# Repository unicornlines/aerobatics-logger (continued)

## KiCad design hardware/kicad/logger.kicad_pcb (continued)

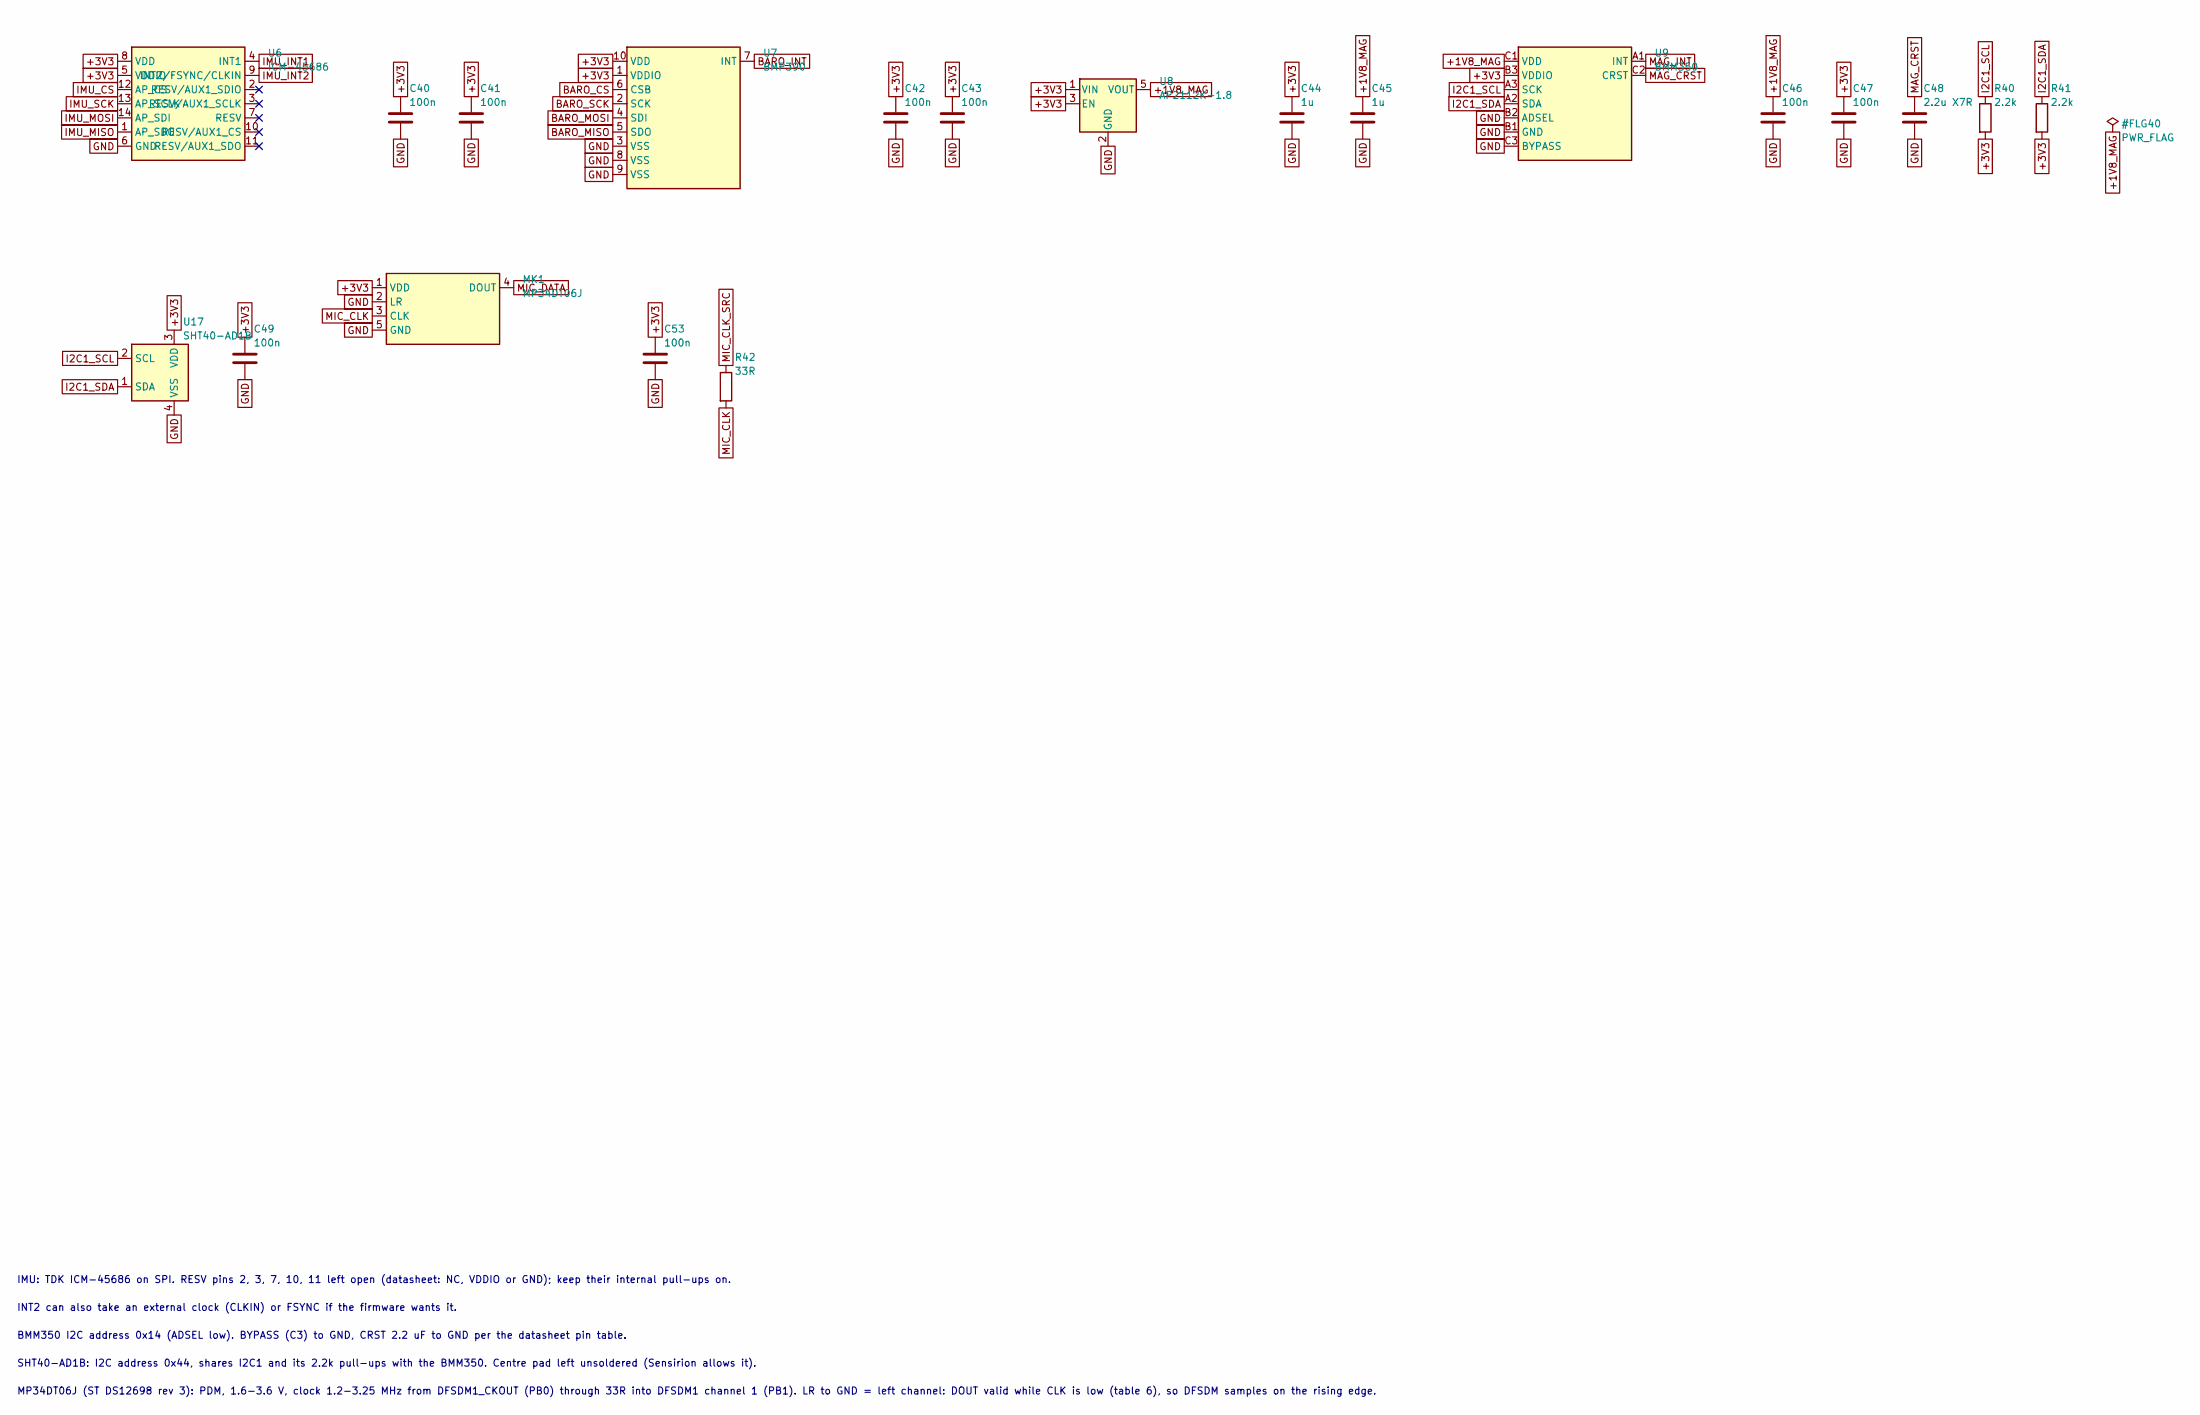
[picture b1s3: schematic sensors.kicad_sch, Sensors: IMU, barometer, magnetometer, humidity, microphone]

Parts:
C40, C41, C42, C43, C46, C47, C49, C53: 100n; C_0402_1005Metric
C44, C45: 1u; C_0402_1005Metric
C48: 2.2u X7R; C_0603_1608Metric
MK1: MP34DT06J; ST_HCLGA-4_3x4mm_MP34DT06J; MPN MP34DT06JTR
R40, R41: 2.2k; R_0402_1005Metric
R42: 33R; R_0402_1005Metric
U6: ICM-45686; LGA-14_3x2.5mm_P0.5mm_LayoutBorder3x4y
U7: BMP390; Bosch_LGA-10_2.0x2.0mm
U8: AP2112K-1.8; SOT-23-5
U9: BMM350; Bosch_WLCSP-9_1.28x1.28mm_P0.4mm
U17: SHT40-AD1B; Sensirion_DFN-4_1.5x1.5mm_P0.8mm_SHT4x_NoCentralPad; MPN SHT40-AD1B-R3

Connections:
+1V8_MAG: C45.1, C46.1, U8.5 (VOUT), U9.C1 (VDD)
+3V3: C40.1, C41.1, C42.1, C43.1, C44.1, C47.1, C49.1, C53.1, MK1.1 (VDD), R40.2, R41.2, U6.5 (VDDIO), U6.8 (VDD), U7.1 (VDDIO), U7.10 (VDD), U8.1 (VIN), U8.3 (EN), U9.B3 (VDDIO), U17.3 (VDD); also elsewhere on the board
BARO_CS: U7.6 (CSB); also elsewhere on the board
BARO_INT: U7.7 (INT); also elsewhere on the board
BARO_MISO: U7.5 (SDO); also elsewhere on the board
BARO_MOSI: U7.4 (SDI); also elsewhere on the board
BARO_SCK: U7.2 (SCK); also elsewhere on the board
GND: C40.2, C41.2, C42.2, C43.2, C44.2, C45.2, C46.2, C47.2, C48.2, C49.2, C53.2, MK1.2 (LR), MK1.5 (GND), MK1.6 (GND), MK1.7 (GND), MK1.8 (GND), U6.6 (GND), U7.3 (VSS), U7.8 (VSS), U7.9 (VSS), U8.2 (GND), U9.B1 (GND), U9.B2 (ADSEL), U9.C3 (BYPASS), U17.4 (VSS); also elsewhere on the board
I2C1_SCL: R40.1, U9.A3 (SCK), U17.2 (SCL); also elsewhere on the board
I2C1_SDA: R41.1, U9.A2 (SDA), U17.1 (SDA); also elsewhere on the board
IMU_CS: U6.12 (AP_CS); also elsewhere on the board
IMU_INT1: U6.4 (INT1); also elsewhere on the board
IMU_INT2: U6.9 (INT2/FSYNC/CLKIN); also elsewhere on the board
IMU_MISO: U6.1 (AP_SDO); also elsewhere on the board
IMU_MOSI: U6.14 (AP_SDI); also elsewhere on the board
IMU_SCK: U6.13 (AP_SCLK); also elsewhere on the board
MAG_CRST: C48.1, U9.C2 (CRST)
MAG_INT: U9.A1 (INT); also elsewhere on the board
MIC_CLK: MK1.3 (CLK), R42.2
MIC_CLK_SRC: R42.1; also elsewhere on the board
MIC_DATA: MK1.4 (DOUT); also elsewhere on the board

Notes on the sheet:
IMU: TDK ICM-45686 on SPI. RESV pins 2, 3, 7, 10, 11 left open (datasheet: NC, VDDIO or GND); keep their internal pull-ups on.
INT2 can also take an external clock (CLKIN) or FSYNC if the firmware wants it.
BMM350 I2C address 0x14 (ADSEL low). BYPASS (C3) to GND, CRST 2.2 uF to GND per the datasheet pin table.
SHT40-AD1B: I2C address 0x44, shares I2C1 and its 2.2k pull-ups with the BMM350. Centre pad left unsoldered (Sensirion allows it).
MP34DT06J (ST DS12698 rev 3): PDM, 1.6-3.6 V, clock 1.2-3.25 MHz from DFSDM1_CKOUT (PB0) through 33R into DFSDM1 channel 1 (PB1). LR to GND = left channel: DOUT valid while CLK is low (table 6), so DFSDM samples on the rising edge.

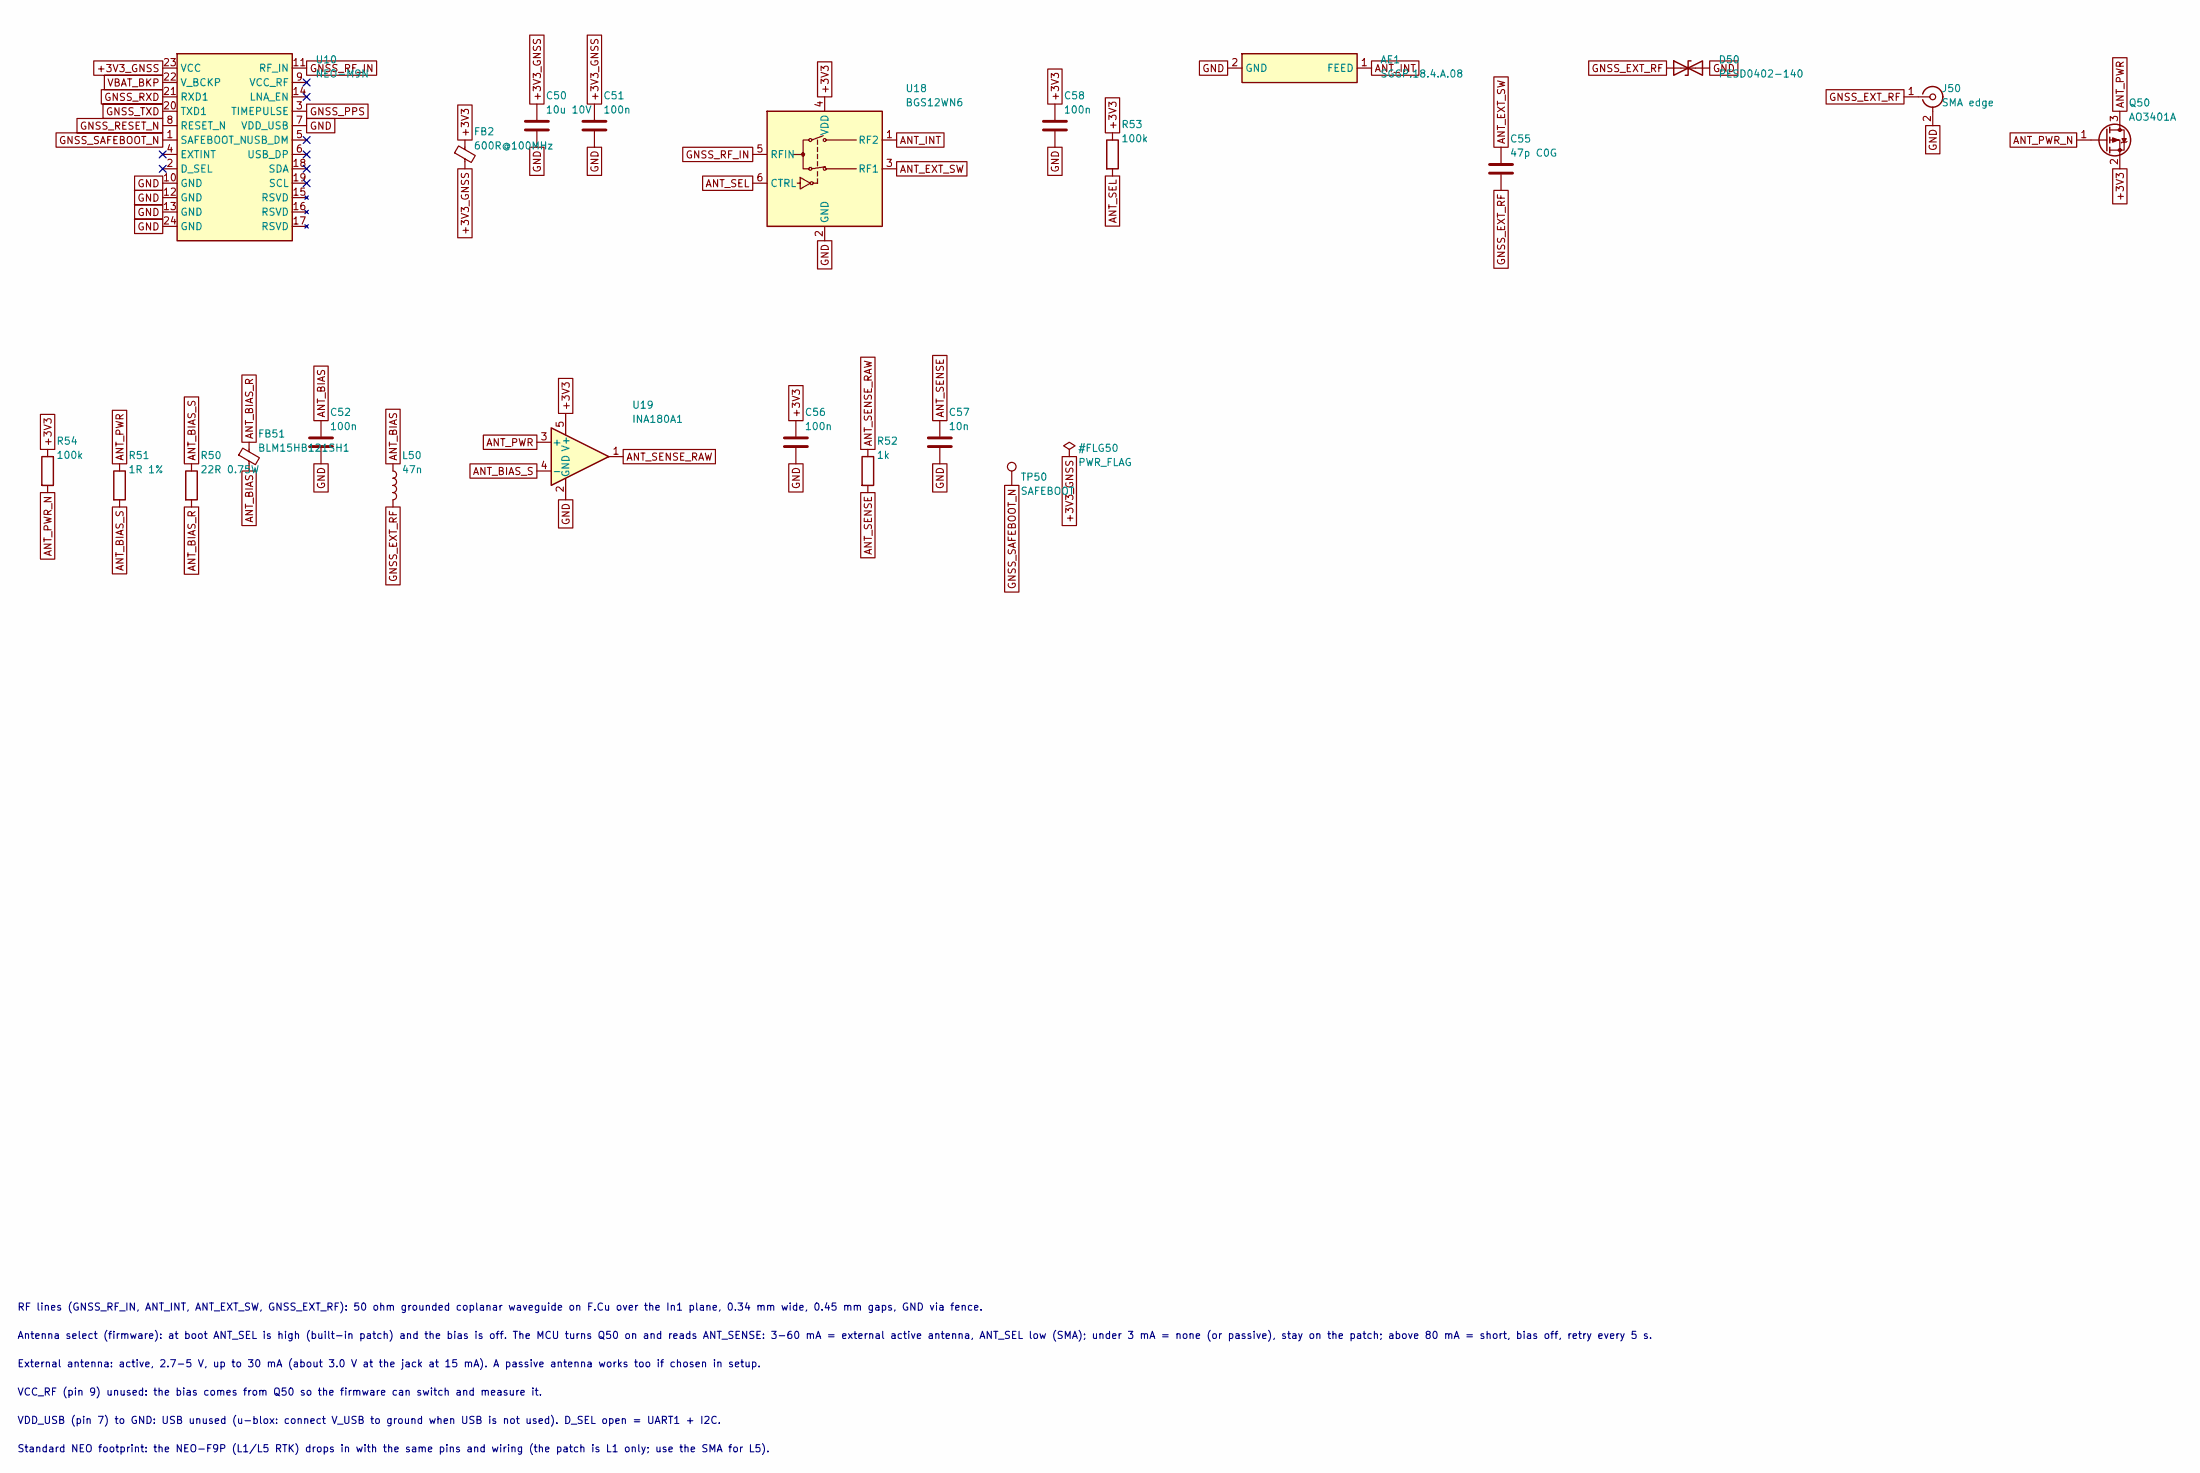
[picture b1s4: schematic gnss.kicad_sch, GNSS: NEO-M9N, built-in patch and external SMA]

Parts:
AE1: SGGP.18.4.A.08; Taoglas_SGGP.18.4.A.08; MPN SGGP.18.4.A.08
C50: 10u 10V; C_0603_1608Metric
C51, C52, C56, C58: 100n; C_0402_1005Metric
C55: 47p C0G; C_0402_1005Metric; MPN GRM1555C1H470JA01D
C57: 10n; C_0402_1005Metric
D50: PESD0402-140; D_0402_1005Metric; MPN PESD0402-140
FB2: 600R@100MHz; L_0603_1608Metric
FB51: BLM15HB121SH1; L_0402_1005Metric; MPN BLM15HB121SH1D
J50: SMA edge; SMA_Samtec_SMA-J-P-X-ST-EM1_EdgeMount; MPN SMA-J-P-H-ST-EM1
L50: 47n; L_0402_1005Metric; MPN LQG15HS47NJ02D
Q50: AO3401A; SOT-23; MPN AO3401A
R50: 22R 0.75W; R_2010_5025Metric
R51: 1R 1%; R_0402_1005Metric
R52: 1k; R_0402_1005Metric
R53, R54: 100k; R_0402_1005Metric
TP50: SAFEBOOT; TestPoint_Pad_D1.0mm
U10: NEO-M9N; ublox_NEO; MPN NEO-M9N-00B
U18: BGS12WN6; Infineon_PG-TSNP-6-10_0.7x1.1mm_0.7x1.1mm_P0.4mm; MPN BGS12WN6E6327XTSA1
U19: INA180A1; SOT-23-5; MPN INA180A1IDBVR

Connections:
+3V3: C56.1, C58.1, FB2.1, Q50.2 (S), R53.1, R54.1, U18.4 (VDD), U19.5 (V+); also elsewhere on the board
+3V3_GNSS: C50.1, C51.1, FB2.2, U10.23 (VCC)
ANT_BIAS: C52.1, FB51.2, L50.1
ANT_BIAS_R: FB51.1, R50.2
ANT_BIAS_S: R50.1, R51.2, U19.4 (-)
ANT_EXT_SW: C55.1, U18.3 (RF1)
ANT_INT: AE1.1 (FEED), U18.1 (RF2)
ANT_PWR: Q50.3 (D), R51.1, U19.3 (+)
ANT_PWR_N: Q50.1 (G), R54.2; also elsewhere on the board
ANT_SEL: R53.2, U18.6 (CTRL); also elsewhere on the board
ANT_SENSE: C57.1, R52.2; also elsewhere on the board
ANT_SENSE_RAW: R52.1, U19.1
GND: AE1.2 (GND), C50.2, C51.2, C52.2, C56.2, C57.2, C58.2, D50.2 (A2), J50.2 (Ext), U10.7 (VDD_USB), U10.10 (GND), U10.12 (GND), U10.13 (GND), U10.24 (GND), U18.2 (GND), U19.2 (GND); also elsewhere on the board
GNSS_EXT_RF: C55.2, D50.1 (A1), J50.1 (In), L50.2
GNSS_PPS: U10.3 (TIMEPULSE); also elsewhere on the board
GNSS_RESET_N: U10.8 (RESET_N); also elsewhere on the board
GNSS_RF_IN: U10.11 (RF_IN), U18.5 (RFIN)
GNSS_RXD: U10.21 (RXD1); also elsewhere on the board
GNSS_SAFEBOOT_N: TP50.1, U10.1 (SAFEBOOT_N)
GNSS_TXD: U10.20 (TXD1); also elsewhere on the board
VBAT_BKP: U10.22 (V_BCKP); also elsewhere on the board

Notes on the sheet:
RF lines (GNSS_RF_IN, ANT_INT, ANT_EXT_SW, GNSS_EXT_RF): 50 ohm grounded coplanar waveguide on F.Cu over the In1 plane, 0.34 mm wide, 0.45 mm gaps, GND via fence.
Antenna select (firmware): at boot ANT_SEL is high (built-in patch) and the bias is off. The MCU turns Q50 on and reads ANT_SENSE: 3-60 mA = external active antenna, ANT_SEL low (SMA); under 3 mA = none (or passive), stay on the patch; above 80 mA = short, bias off, retry every 5 s.
External antenna: active, 2.7-5 V, up to 30 mA (about 3.0 V at the jack at 15 mA). A passive antenna works too if chosen in setup.
VCC_RF (pin 9) unused: the bias comes from Q50 so the firmware can switch and measure it.
VDD_USB (pin 7) to GND: USB unused (u-blox: connect V_USB to ground when USB is not used). D_SEL open = UART1 + I2C.
Standard NEO footprint: the NEO-F9P (L1/L5 RTK) drops in with the same pins and wiring (the patch is L1 only; use the SMA for L5).

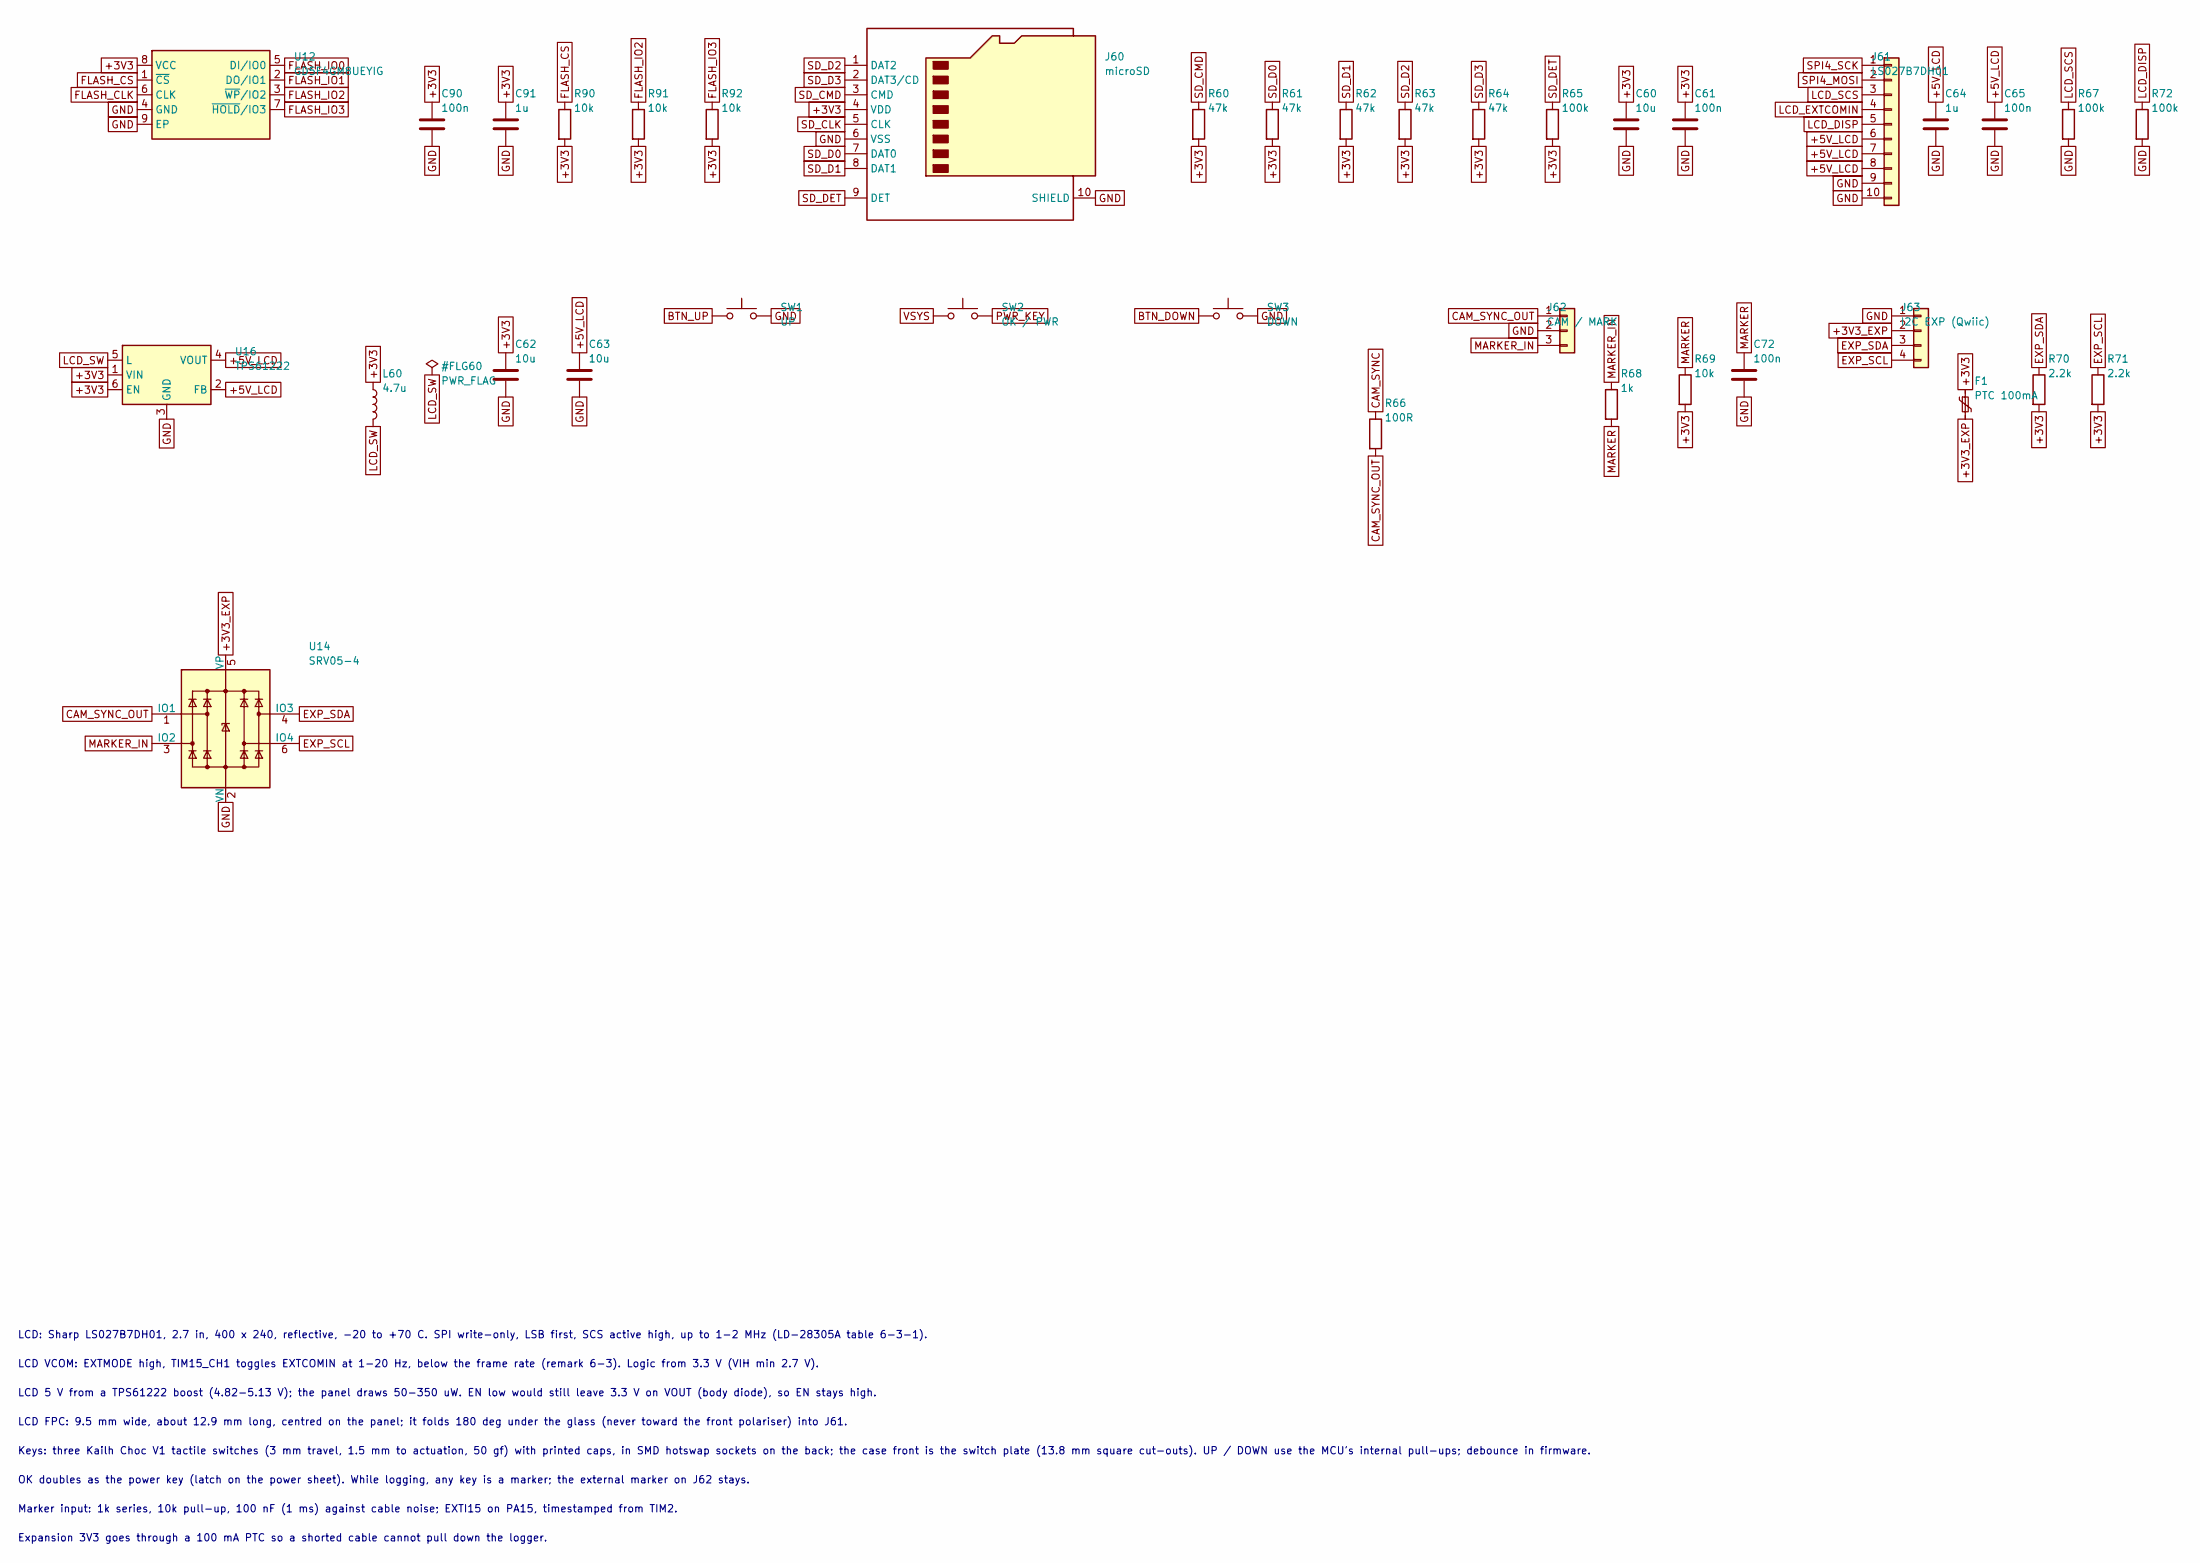
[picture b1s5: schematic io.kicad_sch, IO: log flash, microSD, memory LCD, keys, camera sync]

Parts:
C60: 10u; C_0805_2012Metric
C61, C65, C72, C90: 100n; C_0402_1005Metric
C62, C63: 10u; C_0603_1608Metric
C64, C91: 1u; C_0402_1005Metric
F1: PTC 100mA; Fuse_0603_1608Metric
J60: microSD; microSD_HC_Hirose_DM3AT-SF-PEJM5
J61: LS027B7DH01; Panasonic_AYF531035_1x10-1MP_P0.50mm_Horizontal; MPN AYF531035
J62: CAM / MARK; JST_SUR_SM03B-SURS-TF_1x03-1MP_P0.80mm_Horizontal; MPN SM03B-SURS-TF(LF)(SN)
J63: I2C EXP (Qwiic); JST_SH_SM04B-SRSS-TB_1x04-1MP_P1.00mm_Horizontal; MPN SM04B-SRSS-TB
L60: 4.7u; L_Changjiang_FNR4020S; MPN FNR4020S4R7MT
R60, R61, R62, R63, R64: 47k; R_0402_1005Metric
R65, R67, R72: 100k; R_0402_1005Metric
R66: 100R; R_0402_1005Metric
R68: 1k; R_0402_1005Metric
R69, R90, R91, R92: 10k; R_0402_1005Metric
R70, R71: 2.2k; R_0402_1005Metric
SW1: UP; SW_Kailh_Choc_V1_Hotswap; MPN CPG135001S30
SW2: OK / PWR; SW_Kailh_Choc_V1_Hotswap; MPN CPG135001S30
SW3: DOWN; SW_Kailh_Choc_V1_Hotswap; MPN CPG135001S30
U12: GD5F4GM8UEYIG; WSON-8-1EP_8x6mm_P1.27mm_EP3.4x4.3mm; MPN GD5F4GM8UEYIG
U14: SRV05-4; SOT-23-6; MPN SRV05-4
U16: TPS61222; Texas_R-PDSO-G6; MPN TPS61222DCKR

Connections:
+3V3: C60.1, C61.1, C62.1, C90.1, C91.1, F1.1, J60.4 (VDD), L60.1, R60.2, R61.2, R62.2, R63.2, R64.2, R65.2, R69.2, R70.2, R71.2, R90.2, R91.2, R92.2, U12.8 (VCC), U16.1 (VIN), U16.6 (EN); also elsewhere on the board
+3V3_EXP: F1.2, J63.2, U14.5 (VP)
+5V_LCD: C63.1, C64.1, C65.1, J61.6, J61.7, J61.8, U16.2 (FB), U16.4 (VOUT)
BTN_DOWN: SW3.1; also elsewhere on the board
BTN_UP: SW1.1; also elsewhere on the board
CAM_SYNC: R66.1; also elsewhere on the board
CAM_SYNC_OUT: J62.1, R66.2, U14.1 (IO1)
EXP_SCL: J63.4, R71.1, U14.6 (IO4); also elsewhere on the board
EXP_SDA: J63.3, R70.1, U14.4 (IO3); also elsewhere on the board
FLASH_CLK: U12.6 (CLK); also elsewhere on the board
FLASH_CS: R90.1, U12.1 (~CS); also elsewhere on the board
FLASH_IO0: U12.5 (DI/IO0); also elsewhere on the board
FLASH_IO1: U12.2 (DO/IO1); also elsewhere on the board
FLASH_IO2: R91.1, U12.3 (~WP/IO2); also elsewhere on the board
FLASH_IO3: R92.1, U12.7 (~HOLD/IO3); also elsewhere on the board
GND: C60.2, C61.2, C62.2, C63.2, C64.2, C65.2, C72.2, C90.2, C91.2, J60.6 (VSS), J60.10 (SHIELD), J60.11, J61.9, J61.10, J61.MP, J62.2, J62.MP, J63.1, J63.MP, R67.2, R72.2, SW1.2, SW3.2, U12.4 (GND), U12.9 (EP), U14.2 (VN), U16.3 (GND); also elsewhere on the board
LCD_DISP: J61.5, R72.1; also elsewhere on the board
LCD_EXTCOMIN: J61.4; also elsewhere on the board
LCD_SCS: J61.3, R67.1; also elsewhere on the board
LCD_SW: L60.2, U16.5 (L)
MARKER: C72.1, R68.2, R69.1; also elsewhere on the board
MARKER_IN: J62.3, R68.1, U14.3 (IO2)
PWR_KEY: SW2.2; also elsewhere on the board
SD_CLK: J60.5 (CLK); also elsewhere on the board
SD_CMD: J60.3 (CMD), R60.1; also elsewhere on the board
SD_D0: J60.7 (DAT0), R61.1; also elsewhere on the board
SD_D1: J60.8 (DAT1), R62.1; also elsewhere on the board
SD_D2: J60.1 (DAT2), R63.1; also elsewhere on the board
SD_D3: J60.2 (DAT3/CD), R64.1; also elsewhere on the board
SD_DET: J60.9 (DET), R65.1; also elsewhere on the board
SPI4_MOSI: J61.2; also elsewhere on the board
SPI4_SCK: J61.1; also elsewhere on the board
VSYS: SW2.1; also elsewhere on the board

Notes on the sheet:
LCD: Sharp LS027B7DH01, 2.7 in, 400 x 240, reflective, -20 to +70 C. SPI write-only, LSB first, SCS active high, up to 1-2 MHz (LD-28305A table 6-3-1).
LCD VCOM: EXTMODE high, TIM15_CH1 toggles EXTCOMIN at 1-20 Hz, below the frame rate (remark 6-3). Logic from 3.3 V (VIH min 2.7 V).
LCD 5 V from a TPS61222 boost (4.82-5.13 V); the panel draws 50-350 uW. EN low would still leave 3.3 V on VOUT (body diode), so EN stays high.
LCD FPC: 9.5 mm wide, about 12.9 mm long, centred on the panel; it folds 180 deg under the glass (never toward the front polariser) into J61.
Keys: three Kailh Choc V1 tactile switches (3 mm travel, 1.5 mm to actuation, 50 gf) with printed caps, in SMD hotswap sockets on the back; the case front is the switch plate (13.8 mm square cut-outs). UP / DOWN use the MCU's internal pull-ups; debounce in firmware.
OK doubles as the power key (latch on the power sheet). While logging, any key is a marker; the external marker on J62 stays.
Marker input: 1k series, 10k pull-up, 100 nF (1 ms) against cable noise; EXTI15 on PA15, timestamped from TIM2.
Expansion 3V3 goes through a 100 mA PTC so a shorted cable cannot pull down the logger.

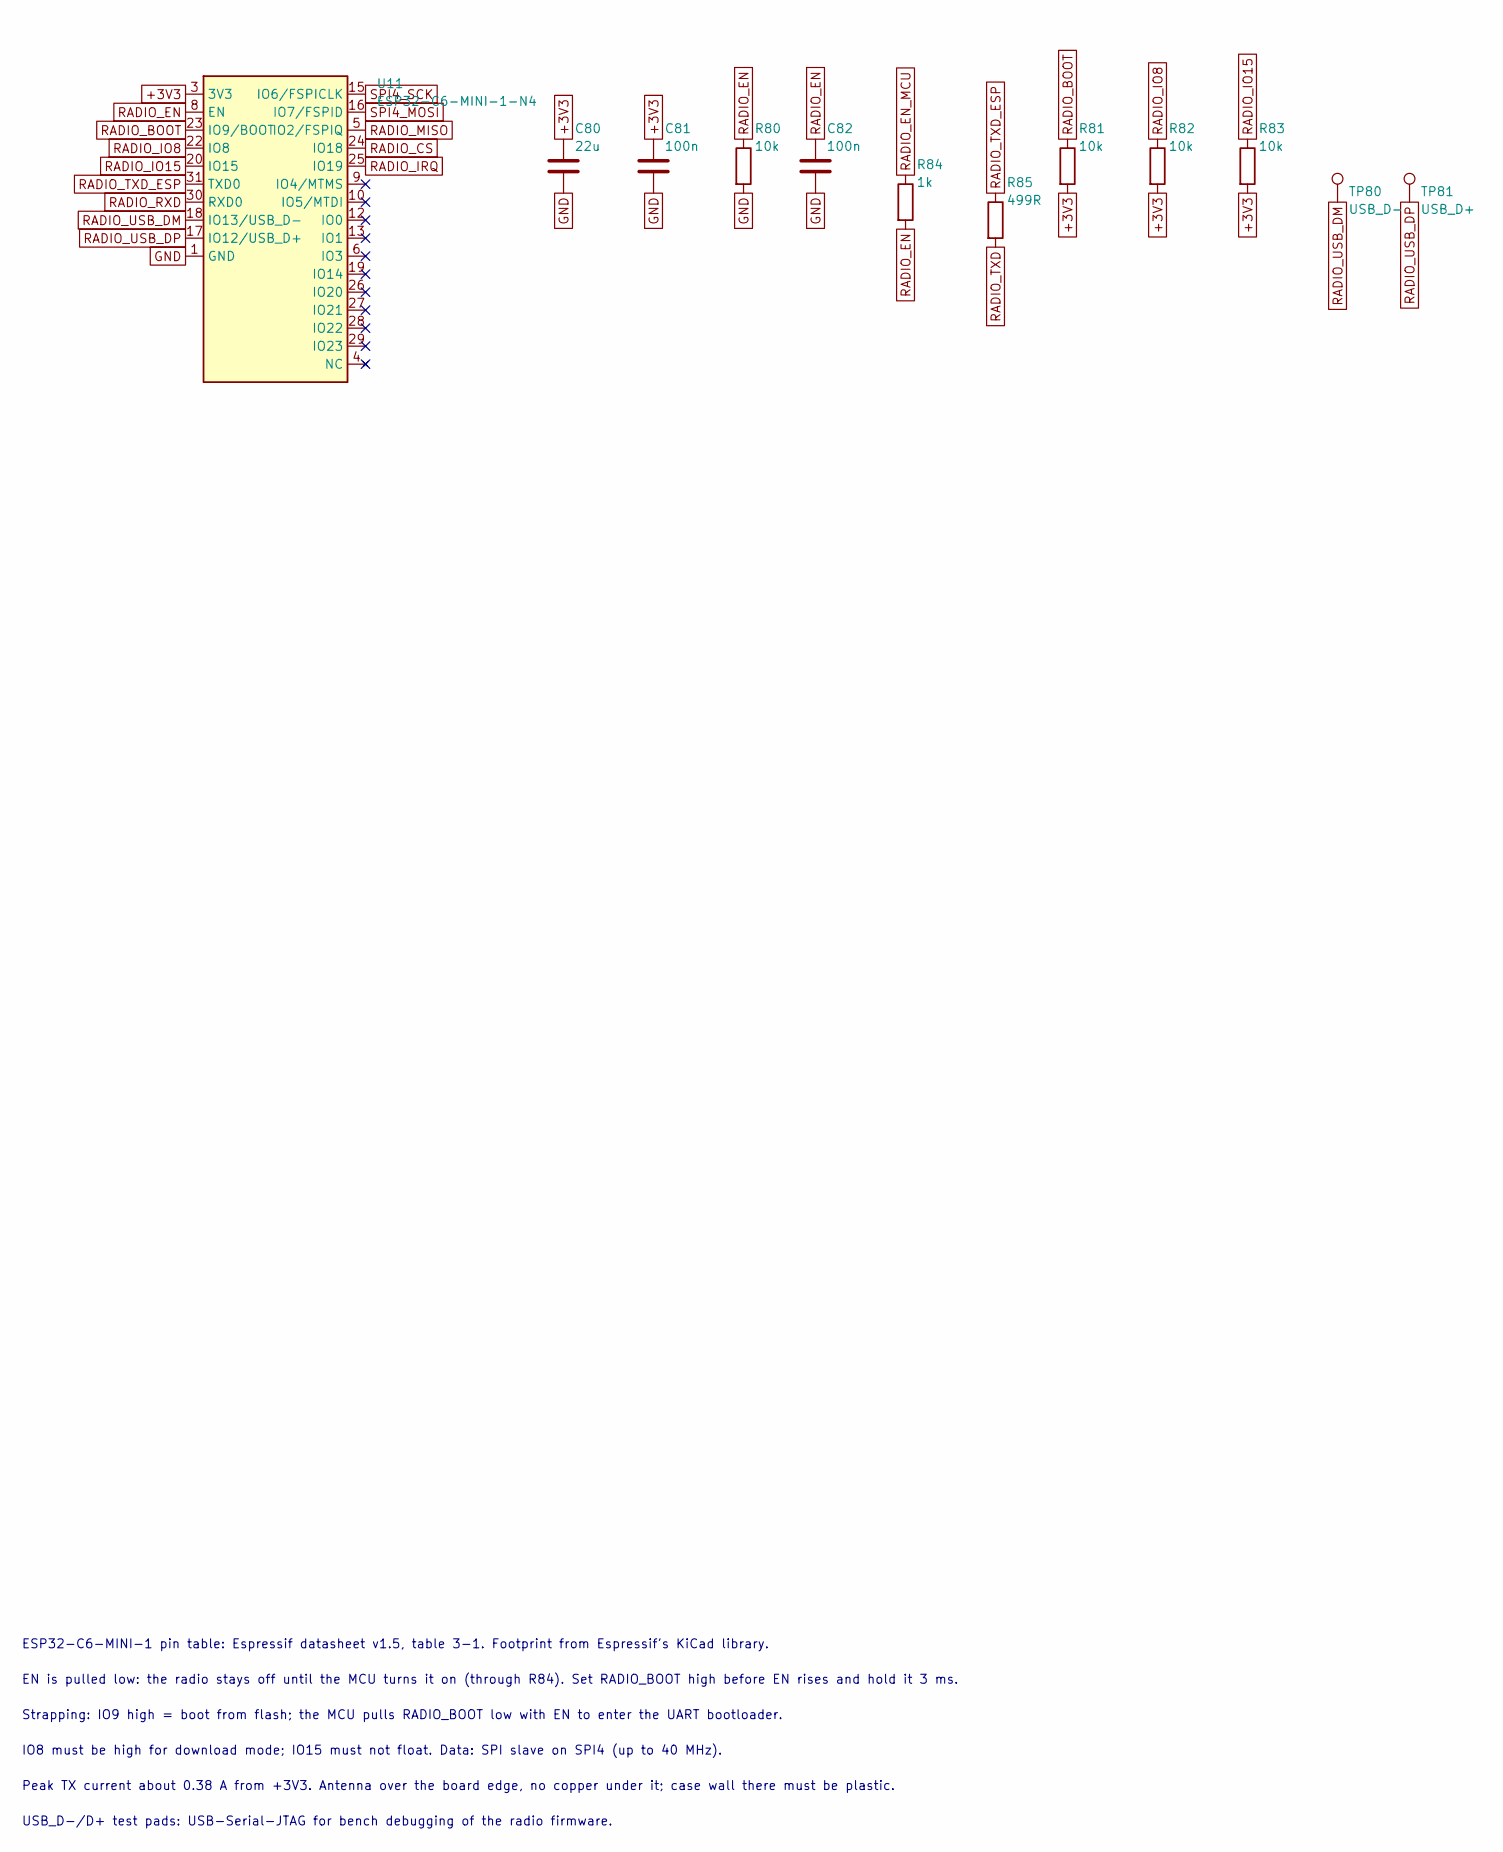
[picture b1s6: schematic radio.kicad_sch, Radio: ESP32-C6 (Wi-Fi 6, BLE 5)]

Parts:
C80: 22u; C_0805_2012Metric
C81, C82: 100n; C_0402_1005Metric
R80, R81, R82, R83: 10k; R_0402_1005Metric
R84: 1k; R_0402_1005Metric
R85: 499R; R_0402_1005Metric
TP80: USB_D-; TestPoint_Pad_D1.0mm
TP81: USB_D+; TestPoint_Pad_D1.0mm
U11: ESP32-C6-MINI-1-N4; ESP32-C6-MINI-1

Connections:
+3V3: C80.1, C81.1, R81.2, R82.2, R83.2, U11.3 (3V3); also elsewhere on the board
GND: C80.2, C81.2, C82.2, R80.2, U11.1 (GND), U11.2 (GND), U11.11 (GND), U11.14 (GND), U11.36 (GND), U11.37 (GND), U11.38 (GND), U11.39 (GND), U11.40 (GND), U11.41 (GND), U11.42 (GND), U11.43 (GND), U11.44 (GND), U11.45 (GND), U11.46 (GND), U11.47 (GND), U11.48 (GND), U11.49 (GND), U11.50 (GND), U11.51 (GND), U11.52 (GND), U11.53 (GND); also elsewhere on the board
RADIO_BOOT: R81.1, U11.23 (IO9/BOOT); also elsewhere on the board
RADIO_CS: U11.24 (IO18); also elsewhere on the board
RADIO_EN: C82.1, R80.1, R84.2, U11.8 (EN)
RADIO_EN_MCU: R84.1; also elsewhere on the board
RADIO_IO8: R82.1, U11.22 (IO8)
RADIO_IO15: R83.1, U11.20 (IO15)
RADIO_IRQ: U11.25 (IO19); also elsewhere on the board
RADIO_MISO: U11.5 (IO2/FSPIQ); also elsewhere on the board
RADIO_RXD: U11.30 (RXD0); also elsewhere on the board
RADIO_TXD: R85.2; also elsewhere on the board
RADIO_TXD_ESP: R85.1, U11.31 (TXD0)
RADIO_USB_DM: TP80.1, U11.18 (IO13/USB_D-)
RADIO_USB_DP: TP81.1, U11.17 (IO12/USB_D+)
SPI4_MOSI: U11.16 (IO7/FSPID); also elsewhere on the board
SPI4_SCK: U11.15 (IO6/FSPICLK); also elsewhere on the board

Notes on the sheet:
ESP32-C6-MINI-1 pin table: Espressif datasheet v1.5, table 3-1. Footprint from Espressif's KiCad library.
EN is pulled low: the radio stays off until the MCU turns it on (through R84). Set RADIO_BOOT high before EN rises and hold it 3 ms.
Strapping: IO9 high = boot from flash; the MCU pulls RADIO_BOOT low with EN to enter the UART bootloader.
IO8 must be high for download mode; IO15 must not float. Data: SPI slave on SPI4 (up to 40 MHz).
Peak TX current about 0.38 A from +3V3. Antenna over the board edge, no copper under it; case wall there must be plastic.
USB_D-/D+ test pads: USB-Serial-JTAG for bench debugging of the radio firmware.

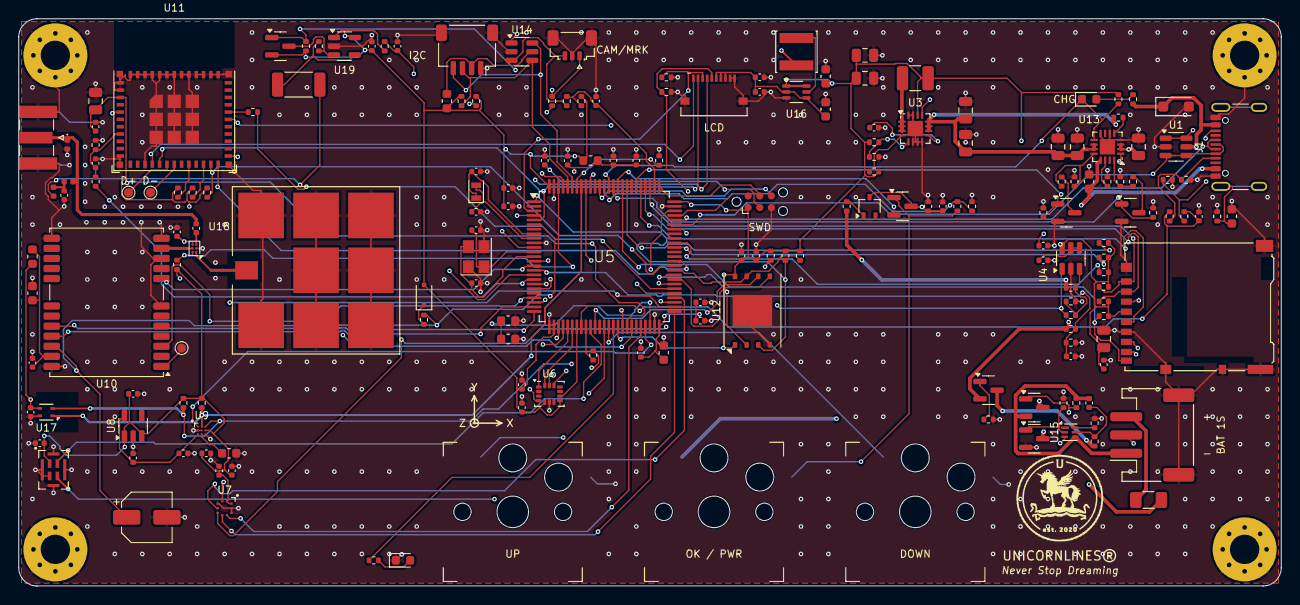
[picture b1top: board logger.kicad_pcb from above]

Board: 4 copper layers, 138.0 x 62.0 mm, 190 parts (0 on the bottom side), 138 nets.

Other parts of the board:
H1, H2, H3, H4: M3; MountingHole_3.2mm_M3_Pad_Via
LOGO1: Unicornlines_Logo

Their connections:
GND: H1.1, H2.1, H3.1, H4.1; also elsewhere on the board

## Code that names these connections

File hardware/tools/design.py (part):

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    R("R116", "100k", "ILIM_HI", "GND"),
    # Safety timer: pre-charge 48 s/k x 71.5k = 57 min, fast charge 10x = 9.5 h. ITERM open: 10 % termination.
    R("R117", "71.5k 1%", "CHG_TMR", "GND"),
    # Charge LED from VBUS (so it can never leak from the cell), CHG also read by the MCU (PD6, 5 V tolerant).
    # The weak pull-up holds the node near 3.3 V when not charging, so the LED sees under 1.7 V and stays dark.
    R("R104", "1.5k", "VBUS", "CHG_LED_A"),
    dict(ref="D22", lib="Device:LED", value="orange", fp="LED_SMD:LED_0603_1608Metric",
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    dict(ref="D24", lib="Diode:BAT54W", value="BAT54W", mpn="BAT54W", fp="Package_TO_SOT_SMD:SOT-323_SC-70",
         nets={"1": "PWR_VBUS", "2": "NC", "3": "PWR_EN"}),
    R("R120", "1M", "PWR_EN", "GND"), C("C110", "1u", "PWR_EN", "GND"),
    # Button sense for the MCU (PD7): 100k / 470k keeps the pin under 3.7 V at VSYS 4.4 V and above VIH at 3.0 V.
    R("R121", "100k", "PWR_KEY", "PWR_BTN"), R("R122", "470k", "PWR_BTN", "GND"),
    # Battery: JST PH 3-pin (1 cell -, 2 NTC, 3 cell +), fuse, reverse-polarity PMOS (conducts both ways once its
    # body diode lets the gate see -VBAT).
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    "24": "GNSS_RXD", "25": "GNSS_TXD", "15": "GNSS_RESET_N",
    # microSD on SDMMC1
    "65": "SD_D0", "66": "SD_D1", "78": "SD_D2", "79": "SD_D3", "80": "SD_CLK", "83": "SD_CMD", "84": "SD_DET",
    # SPI4: memory LCD and the radio share SCK/MOSI; LCD chip select is active high (SCS). MISO (PE13) is the radio's only.
    # EXTCOMIN on PE5 = TIM15_CH1, so a timer toggles the LCD's VCOM with no CPU; DISP on PD10.
    "42": "SPI4_SCK", "5": "SPI4_MOSI", "3": "LCD_SCS", "4": "LCD_EXTCOMIN", "57": "LCD_DISP",
    "43": "RADIO_MISO", "62": "RADIO_CS", "44": "RADIO_IRQ",
    # log flash on OCTOSPI1 in quad mode: CLK PB2, NCS PE11, IO0 PD11, IO1 PD12, IO2 PE2, IO3 PD13
    "36": "FLASH_CLK", "41": "FLASH_CS", "58": "FLASH_IO0", "59": "FLASH_IO1", "1": "FLASH_IO2", "60": "FLASH_IO3",
    # radio control and its UART0 (USART3: bootloader, console); names from the module's side.
    # RADIO_EN_MCU on PC3_C: a static enable line, so it runs as a GPIO through the closed PC3 analog
    # switch (firmware clears SYSCFG_PMCR.PC3SO); until then the pin floats and the radio's own EN RC holds it.
    "18": "RADIO_EN_MCU", "61": "RADIO_BOOT", "55": "RADIO_RXD", "56": "RADIO_TXD",
    # buttons, power fail, camera sync, LED
    # keys: UP on PE8 (EXTI8), DOWN on PE9 (EXTI9); OK is the power key and is read on PD7 (PWR_BTN, EXTI7).
    # Every EXTI line has one pin only: PWR_FAIL_N on PA10 (EXTI10), marker PA15 (EXTI15), IMU INT2 PC4 (EXTI4).
    "38": "BTN_UP", "39": "BTN_DOWN", "69": "PWR_FAIL_N",
    # power latch and charger: PD4 hold, PD7 button sense, PD6 CHG status, PD5 / PD0 charge and input current steps
    "85": "PWR_HOLD", "88": "PWR_BTN", "87": "CHG_STAT_N", "86": "ISET_HI", "81": "ILIM_HI",
    # ADC: battery voltage (PC1, ADC1_INP11) and the USB-C CC level (PC5, ADC12_INP8)
    "16": "VBAT_SENSE", "33": "CC_SENSE", "91": "CAM_SYNC", "40": "LED_STATUS",   # camera sync on PB5 = TIM3_CH2
    # GNSS antenna: RF switch select on PE1 and feed switch on PE0 (top-left corner, toward Q50; low = on),
    # feed current on PC2_C (ADC3_INP0)
    "98": "ANT_SEL", "97": "ANT_PWR_N", "17": "ANT_SENSE",
    # PDM microphone on DFSDM1 channel 1: the DFSDM's own clock out on PB0 (DFSDM1_CKOUT), data in on PB1
    # (DFSDM1_DATIN1). Both sit on the MCU's bottom-left side, toward the mic; clear of the PC2_C/PC3_C analog switch.
    "34": "MIC_CLK_SRC", "35": "MIC_DATA",
    # USB and debug
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    "INT2 can also take an external clock (CLKIN) or FSYNC if the firmware wants it.",
    "BMM350 I2C address 0x14 (ADSEL low). BYPASS (C3) to GND, CRST 2.2 uF to GND per the datasheet pin table.",
    "SHT40-AD1B: I2C address 0x44, shares I2C1 and its 2.2k pull-ups with the BMM350. Centre pad left unsoldered (Sensirion allows it).",
    "MP34DT06J (ST DS12698 rev 3): PDM, 1.6-3.6 V, clock 1.2-3.25 MHz from DFSDM1_CKOUT (PB0) through 33R into DFSDM1 channel 1 (PB1). LR to GND = left channel: DOUT valid while CLK is low (table 6), so DFSDM samples on the rising edge.",
])

# ---------------------------------------------------------------- GNSS
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         nets={"1": "+3V3", "2": "+5V_LCD", "3": "GND", "4": "+5V_LCD", "5": "LCD_SW", "6": "+3V3"}),
    dict(ref="L60", lib="Device:L", value="4.7u", fp="Inductor_SMD:L_Changjiang_FNR4020S", mpn="FNR4020S4R7MT",
         nets={"1": "+3V3", "2": "LCD_SW"}),
    FLAG("#FLG60", "LCD_SW"),   # KiCad's symbol calls the L pin a power input; the inductor drives it
    C("C62", "10u", "+3V3", "GND", fp=C0603), C("C63", "10u", "+5V_LCD", "GND", fp=C0603),
    # Keys: three Kailh Choc V1 tactile switches (brown, CPG135001D02) with printed caps, pressed from the front. The board
    # carries only the Kailh hotswap sockets (CPG135001S30, JLCPCB C5333465, SMD on the back); the switches are pressed in at
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    "LCD FPC: 9.5 mm wide, about 12.9 mm long, centred on the panel; it folds 180 deg under the glass (never toward the front polariser) into J61.",
    "Keys: three Kailh Choc V1 tactile switches (3 mm travel, 1.5 mm to actuation, 50 gf) with printed caps, in SMD hotswap sockets on the back; the case front is the switch plate (13.8 mm square cut-outs). UP / DOWN use the MCU's internal pull-ups; debounce in firmware.",
    "OK doubles as the power key (latch on the power sheet). While logging, any key is a marker; the external marker on J62 stays.",
    "Marker input: 1k series, 10k pull-up, 100 nF (1 ms) against cable noise; EXTI15 on PA15, timestamped from TIM2.",
    "Expansion 3V3 goes through a 100 mA PTC so a shorted cable cannot pull down the logger.",
])

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], notes=[
    "ESP32-C6-MINI-1 pin table: Espressif datasheet v1.5, table 3-1. Footprint from Espressif's KiCad library.",
    "EN is pulled low: the radio stays off until the MCU turns it on (through R84). Set RADIO_BOOT high before EN rises and hold it 3 ms.",
    "Strapping: IO9 high = boot from flash; the MCU pulls RADIO_BOOT low with EN to enter the UART bootloader.",
    "IO8 must be high for download mode; IO15 must not float. Data: SPI slave on SPI4 (up to 40 MHz).",
    "Peak TX current about 0.38 A from +3V3. Antenna over the board edge, no copper under it; case wall there must be plastic.",
    "USB_D-/D+ test pads: USB-Serial-JTAG for bench debugging of the radio firmware.",
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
